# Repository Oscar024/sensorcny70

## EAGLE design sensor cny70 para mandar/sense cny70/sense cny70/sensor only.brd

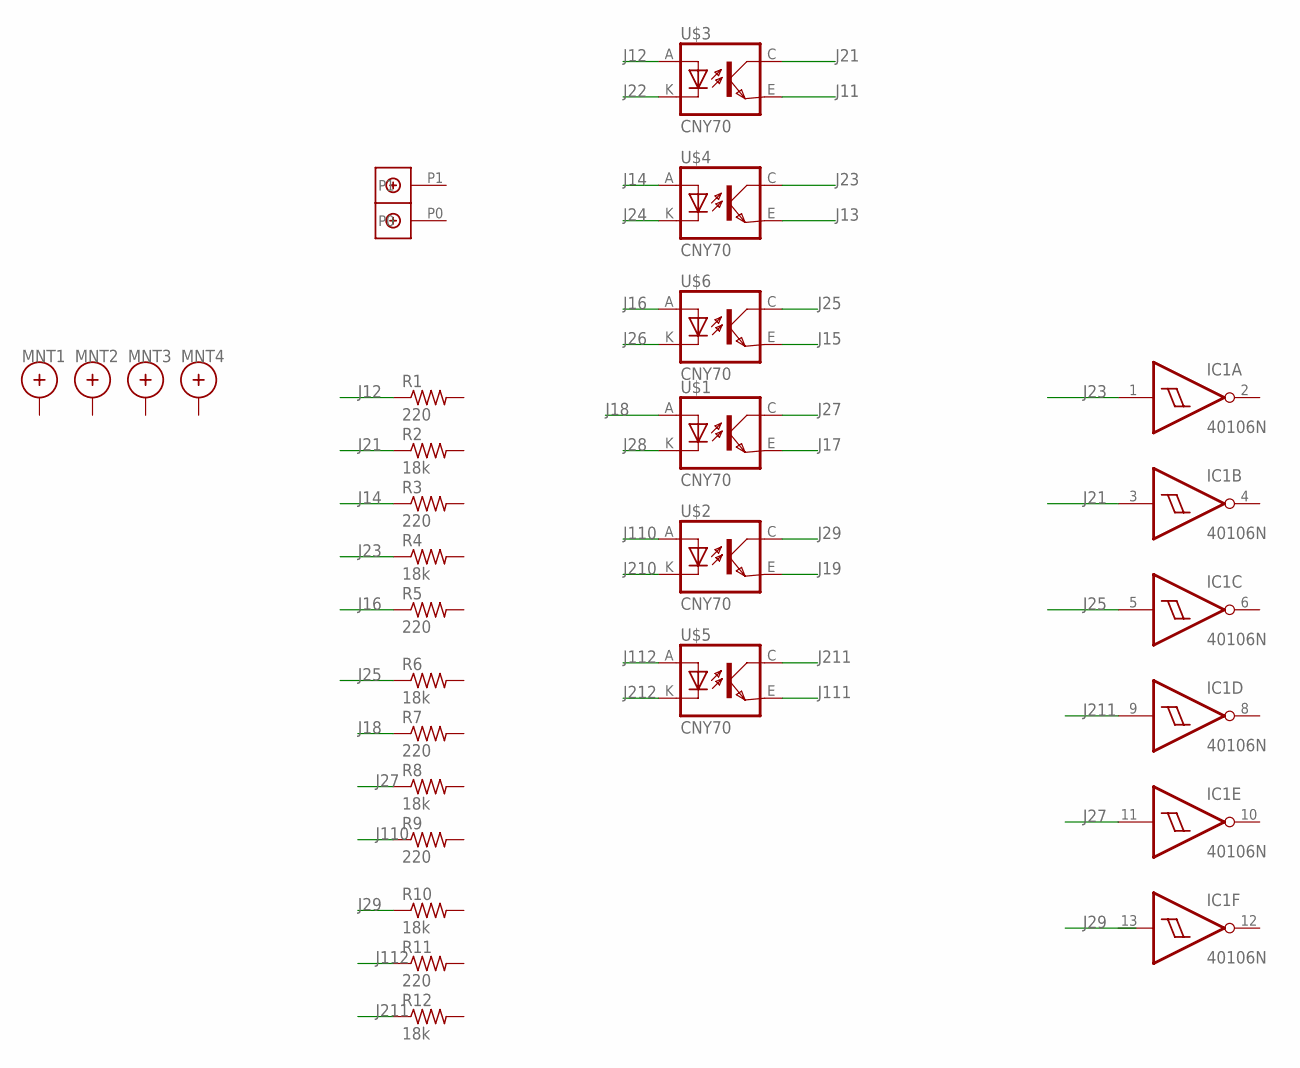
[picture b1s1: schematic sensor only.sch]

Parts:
IC1: 40106N; DIL14
MNT1, MNT2, MNT3, MNT4: HOLE_MNT_0.135; HOLE_MNT_#5-40
R1, R3, R5, R7, R9, R11: 220; 0309/10
R2, R4, R6, R8, R10, R12: 18k; 0309/10
U$1, U$2, U$3, U$4, U$5, U$6: CNY70; 4
U$7: DBCONN-1X2

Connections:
J11: U$3.E (EMI)
J12: R1.1, U$3.A
J13: U$4.E (EMI)
J14: R3.1, U$4.A
J15: U$6.E (EMI)
J16: R5.1, U$6.A
J17: U$1.E (EMI)
J18: R7.1, U$1.A
J19: U$2.E (EMI)
J21: IC1.3 (I), R2.1, U$3.C (COL)
J22: U$3.K (C)
J23: IC1.1 (I), R4.1, U$4.C (COL)
J24: U$4.K (C)
J25: IC1.5 (I), R6.1, U$6.C (COL)
J26: U$6.K (C)
J27: IC1.11 (I), R8.1, U$1.C (COL)
J28: U$1.K (C)
J29: R10.1, U$2.C (COL)
J110: R9.1, U$2.A
J111: U$5.E (EMI)
J112: R11.1, U$5.A
J210: U$2.K (C)
J211: IC1.9 (I), R12.1, U$5.C (COL)
J212: U$5.K (C)
VDD: IC1.14 (VDD)
VSS: IC1.7 (VSS)

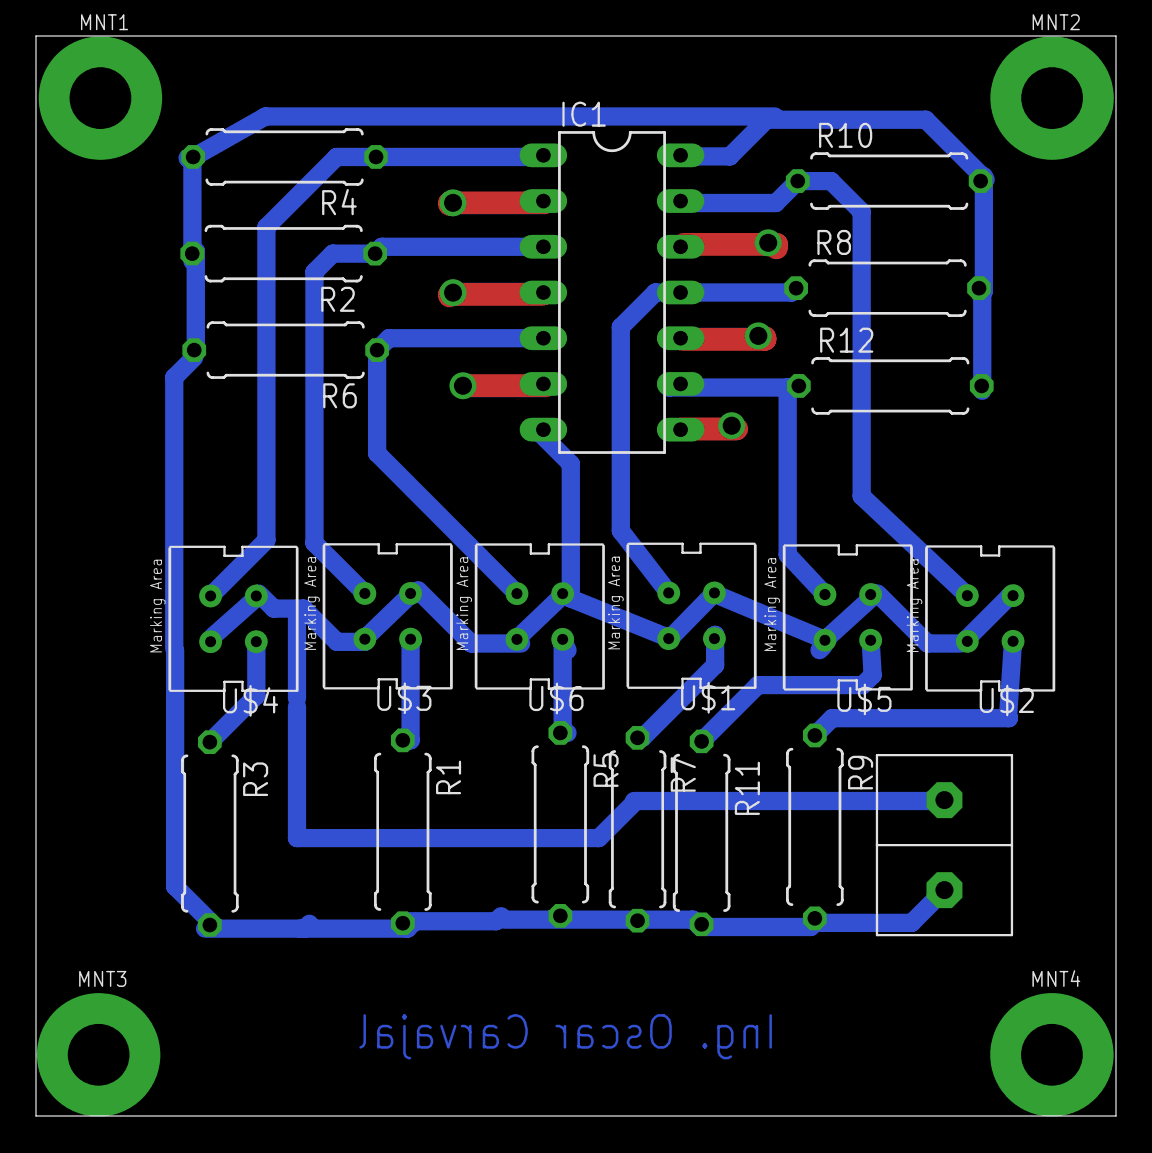
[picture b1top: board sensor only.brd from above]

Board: 2 copper layers, 60.0 x 60.0 mm, 24 parts (0 on the bottom side), 12 nets.
